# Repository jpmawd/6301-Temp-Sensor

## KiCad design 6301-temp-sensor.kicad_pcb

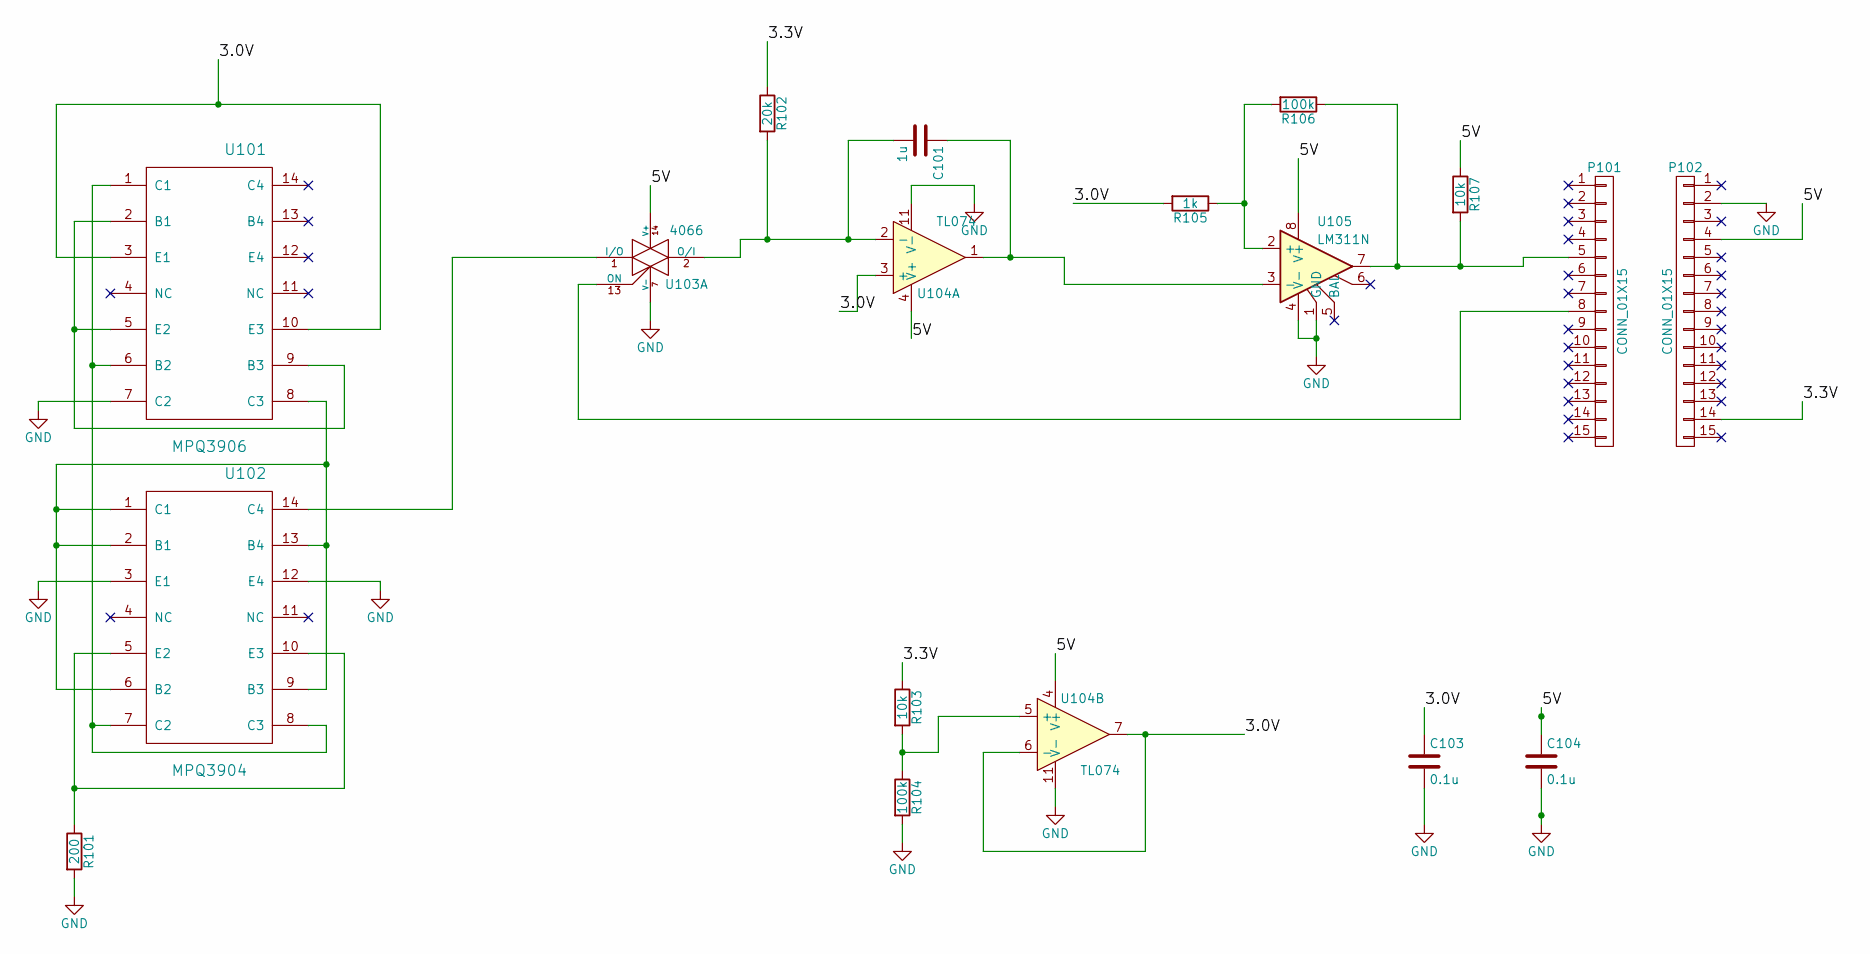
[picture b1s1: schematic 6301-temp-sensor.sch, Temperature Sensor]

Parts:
C101: 1u; C_Rect_L7_W2.5_P5
C103, C104: 0.1u; C_Disc_D3_P2.5
P101, P102: CONN_01X15; Socket_Strip_Straight_1x15
R101: 200; Resistor_Horizontal_RM10mm
R102: 20k; Resistor_Horizontal_RM10mm
R103, R107: 10k; Resistor_Horizontal_RM10mm
R104, R106: 100k; Resistor_Horizontal_RM10mm
R105: 1k; Resistor_Horizontal_RM10mm
U101: MPQ3906; DIP-14_W7.62mm
U102: MPQ3904; DIP-14_W7.62mm
U103: 4066; DIP-14_W7.62mm
U104: TL074; DIP-14_W7.62mm
U105: LM311N; DIP-8_W7.62mm

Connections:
/3.0V: C103.1, R105.2, U101.3 (E1), U101.10 (E3), U104.3 (+), U104.6 (-), U104.7
/3.3V: P102.14, R102.1, R103.1
/5V: C104.1, P102.4, R107.1, U103.14 (V+), U104.4 (V+), U105.8 (V+)
GND: C103.2, C104.2, P102.2, R101.2, R104.2, U101.7 (C2), U102.3 (E1), U102.12 (E4), U103.7 (V-), U104.11 (V-), U105.1 (GND), U105.4 (V-)
unnamed: C101.1, U104.1, U105.3 (-)
unnamed: C101.2, R102.2, U103.2 (O/I), U104.2 (-)
unnamed: P101.5, R106.1, R107.2, U105.7
unnamed: P101.8, U103.13 (ON)
unnamed: R101.1, U102.5 (E2), U102.10 (E3)
unnamed: R103.2, R104.1, U104.5 (+)
unnamed: R105.1, R106.2, U105.2 (+)
unnamed: U101.1 (C1), U101.6 (B2), U102.7 (C2), U102.8 (C3)
unnamed: U101.2 (B1), U101.5 (E2), U101.9 (B3)
unnamed: U101.8 (C3), U102.1 (C1), U102.2 (B1), U102.6 (B2), U102.9 (B3), U102.13 (B4)
unnamed: U102.14 (C4), U103.1 (I/O)

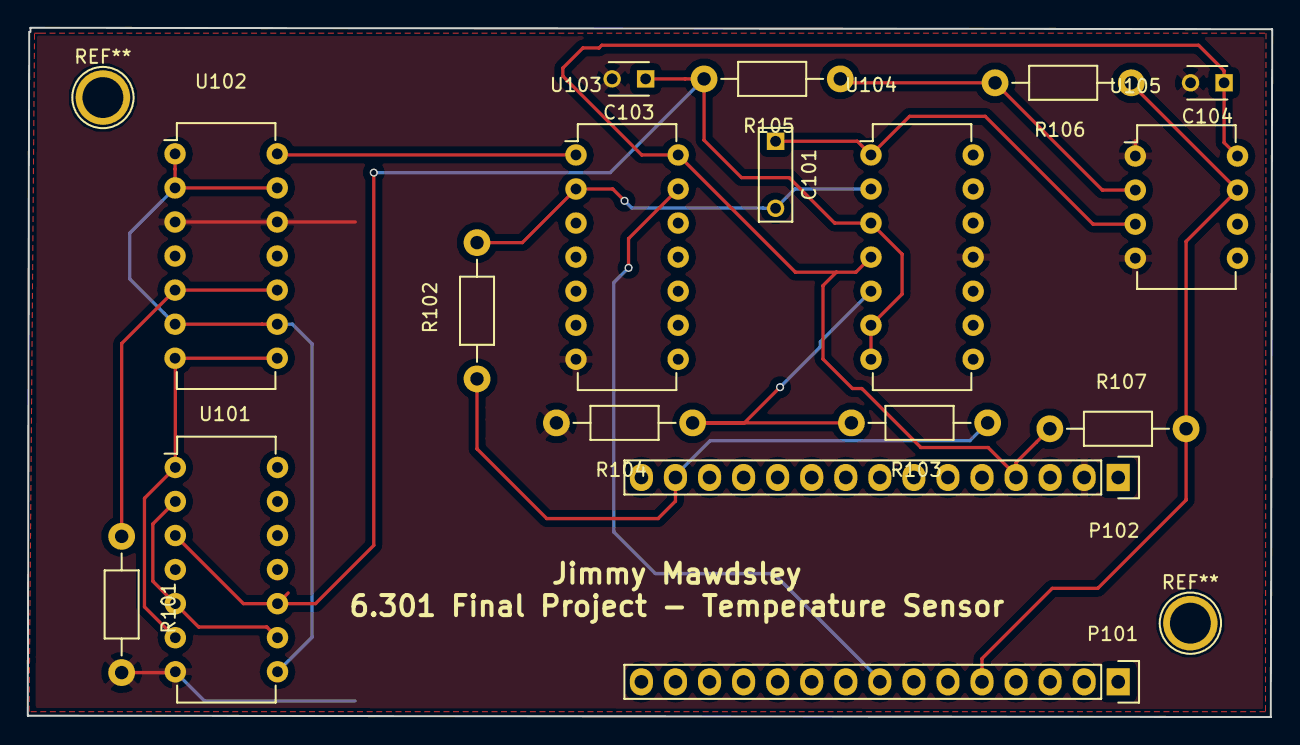
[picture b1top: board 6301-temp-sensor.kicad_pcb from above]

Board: 2 copper layers, 92.8 x 51.4 mm, 17 parts (0 on the bottom side), 15 nets.

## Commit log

2016-12-05 initial commit of schematic, layout, gerbers
2016-12-11 fixed schematic and layout
2016-12-13 More fixes
